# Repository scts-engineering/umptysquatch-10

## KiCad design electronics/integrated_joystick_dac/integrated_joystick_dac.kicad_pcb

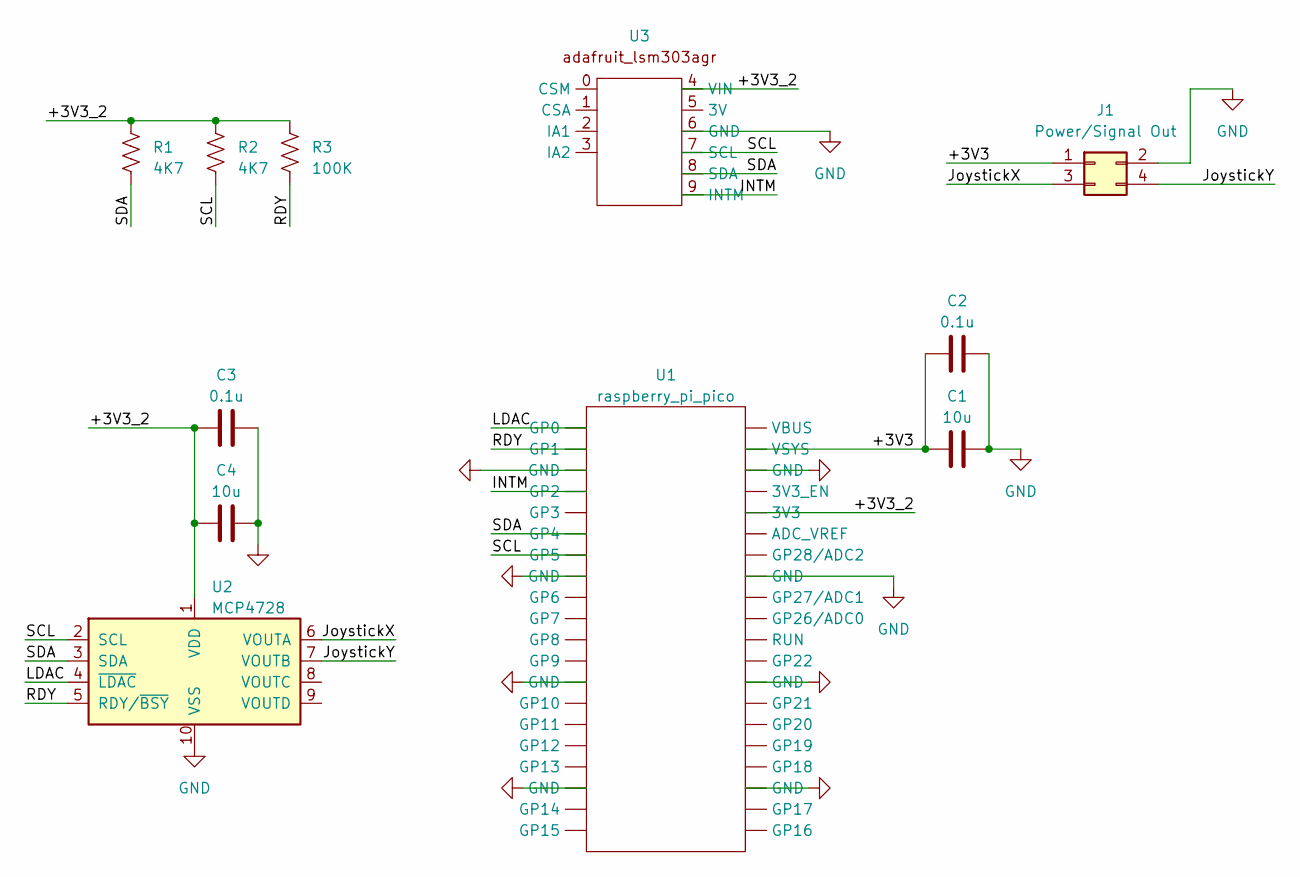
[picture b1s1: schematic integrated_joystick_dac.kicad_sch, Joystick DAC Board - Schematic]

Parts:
C1, C4: 10u; C_0603_1608Metric_Pad1.08x0.95mm_HandSolder
C2, C3: 0.1u; C_0402_1005Metric_Pad0.74x0.62mm_HandSolder
J1: Power/Signal Out; Molex_Mini-Fit_Jr_5569-04A2_2x02_P4.20mm_Horizontal
R1, R2: 4K7; R_Axial_DIN0207_L6.3mm_D2.5mm_P10.16mm_Horizontal
R3: 100K; R_Axial_DIN0207_L6.3mm_D2.5mm_P10.16mm_Horizontal
U1: raspberry_pi_pico
U2: MCP4728; MSOP-10_3x3mm_P0.5mm
U3: adafruit_lsm303agr

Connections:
/+3V3: C1.1, C2.1, J1.1, U1.39 (VSYS)
/+3V3_2: C3.1, C4.1, R1.1, R2.1, R3.1, U1.36 (3V3), U2.1 (VDD), U3.4 (VIN)
/INTM: U1.4 (GP2), U3.9 (INTM)
/JoystickX: J1.3, U2.6 (VOUTA)
/JoystickY: J1.4, U2.7 (VOUTB)
/LDAC: U1.1 (GP0), U2.4 (~LDAC)
/RDY: R3.2, U1.2 (GP1), U2.5 (RDY/~BSY)
/SCL: R2.2, U1.7 (GP5), U2.2 (SCL), U3.7 (SCL)
/SDA: R1.2, U1.6 (GP4), U2.3 (SDA), U3.8 (SDA)
GND: C1.2, C2.2, C3.2, C4.2, J1.2, U1.3 (GND), U1.8 (GND), U1.13 (GND), U1.18 (GND), U1.23 (GND), U1.28 (GND), U1.33 (GND), U1.38 (GND), U2.10 (VSS), U3.6 (GND)

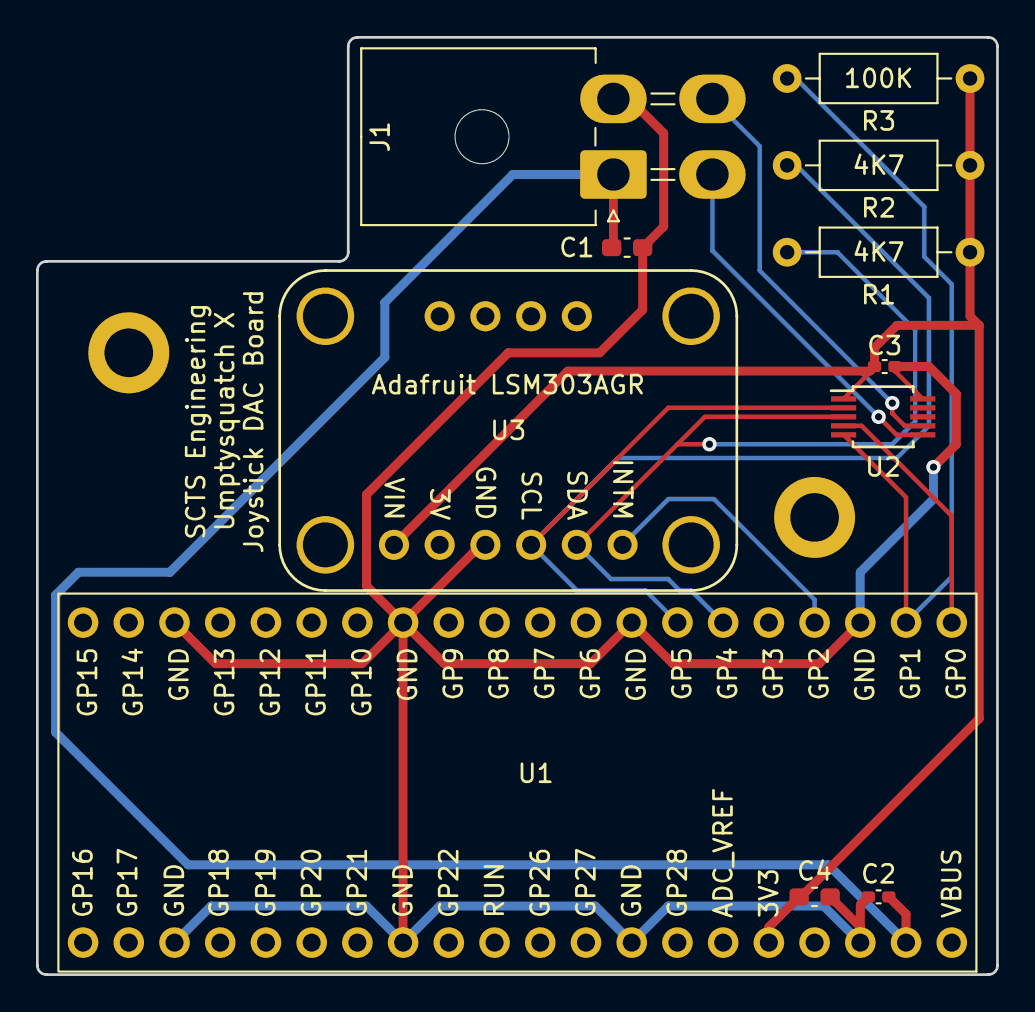
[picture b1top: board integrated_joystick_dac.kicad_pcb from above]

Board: 2 copper layers, 53.3 x 52.1 mm, 11 parts (0 on the bottom side), 10 nets.

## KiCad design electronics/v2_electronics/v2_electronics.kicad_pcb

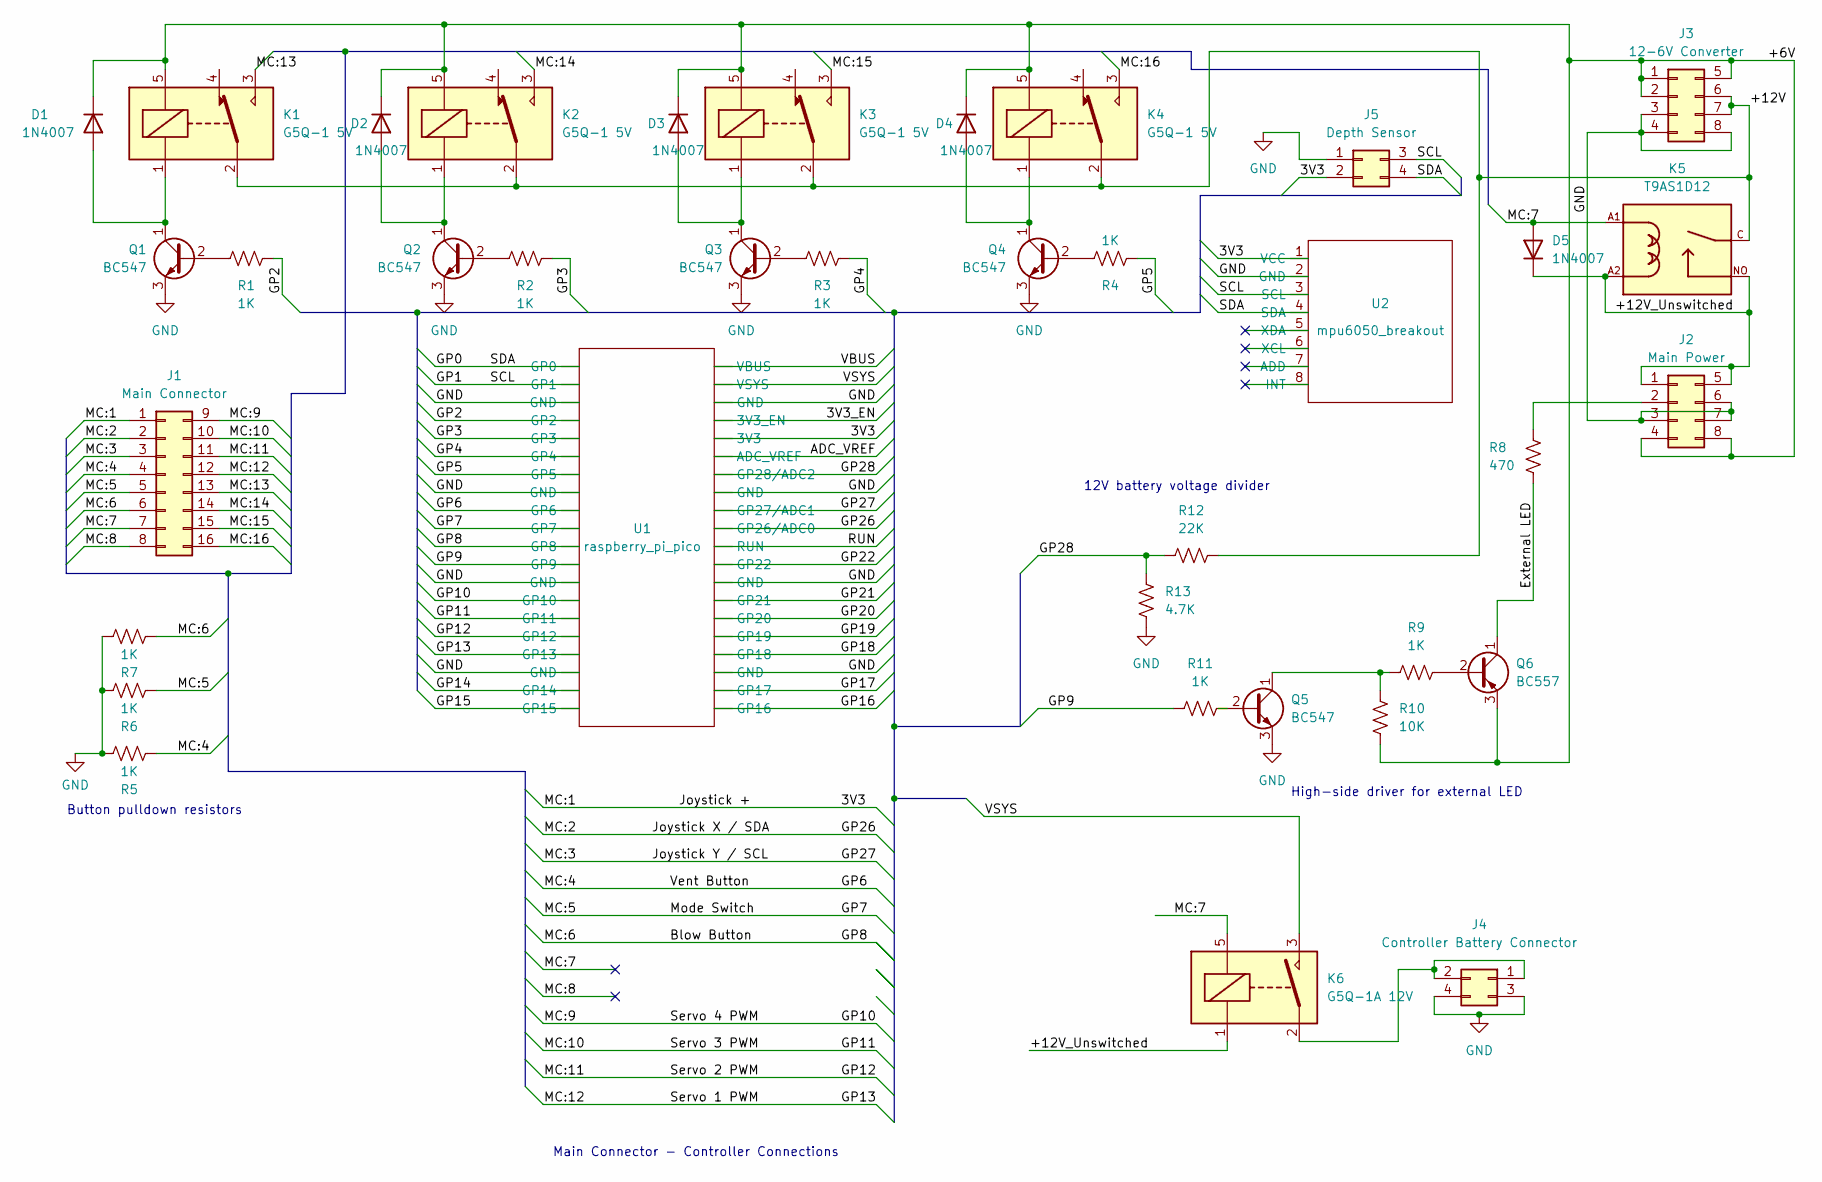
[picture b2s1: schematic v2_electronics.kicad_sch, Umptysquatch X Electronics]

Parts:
D1, D2, D3, D4: 1N4007; D_DO-41_SOD81_P12.70mm_Horizontal
D5: 1N4007; D_DO-41_SOD81_P10.16mm_Horizontal
J1: Main Connector; Molex_Mini-Fit_Jr_5569-16A2_2x08_P4.20mm_Horizontal
J2: Main Power; Molex_Mini-Fit_Jr_5569-08A2_2x04_P4.20mm_Horizontal
J3: 12-6V Converter; Molex_Mini-Fit_Jr_5569-08A2_2x04_P4.20mm_Horizontal
J4: Controller Battery Connector; Molex_Mini-Fit_Jr_5569-04A2_2x02_P4.20mm_Horizontal
J5: Depth Sensor; Molex_Mini-Fit_Jr_5569-04A2_2x02_P4.20mm_Horizontal
K1, K2, K3, K4: G5Q-1 5V; Relay_SPDT_Omron-G5Q-1
K5: T9AS1D12
K6: G5Q-1A 12V; Relay_SPST_Omron-G5Q-1A
Q1, Q2, Q3, Q4, Q5: BC547; TO-92_Inline
Q6: BC557; TO-92_Inline
R1, R2, R3, R4, R5, R6, R7, R9, R11: 1K; R_Axial_DIN0207_L6.3mm_D2.5mm_P10.16mm_Horizontal
R8: 470; R_Axial_DIN0207_L6.3mm_D2.5mm_P10.16mm_Horizontal
R10: 10K; R_Axial_DIN0207_L6.3mm_D2.5mm_P10.16mm_Horizontal
R12: 22K; R_Axial_DIN0207_L6.3mm_D2.5mm_P10.16mm_Horizontal
R13: 4.7K; R_Axial_DIN0207_L6.3mm_D2.5mm_P10.16mm_Horizontal
U1: raspberry_pi_pico
U2: mpu6050_breakout; mpu6050

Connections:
/3V3: J1.1, J5.2, U1.36 (3V3), U2.1 (VCC)
/3V3_EN: U1.37 (3V3_EN); also elsewhere on the board
/+6V: D1.1 (K), D2.1 (K), D3.1 (K), D4.1 (K), J2.4, J2.8, J3.1, J3.2, J3.5, K1.5, K2.5, K3.5, K4.5, Q6.3 (E), R10.1
/+12V: J3.6, J3.7, K1.2, K2.2, K3.2, K4.2, K5.C, R12.2
/+12V_Unswitched: D5.1 (K), J2.1, J2.5, K5.A2, K5.NO, K6.1
/ADC_VREF: U1.35 (ADC_VREF); also elsewhere on the board
/Blow Button: J1.6, R7.2, U1.11 (GP8)
/External LED: Q6.1 (C), R8.1
/GP0: J5.4, U1.1 (GP0), U2.4 (SDA)
/GP1: J5.3, U1.2 (GP1), U2.3 (SCL)
/GP2: R1.2, U1.4 (GP2)
/GP3: R2.2, U1.5 (GP3)
/GP4: R3.2, U1.6 (GP4)
/GP5: R4.2, U1.7 (GP5)
/GP6: J1.4, R5.2, U1.9 (GP6)
/GP7: J1.5, R6.2, U1.10 (GP7)
/GP9: R11.1, U1.12 (GP9)
/GP10: J1.9, U1.14 (GP10)
/GP11: J1.10, U1.15 (GP11)
/GP12: J1.11, U1.16 (GP12)
/GP13: J1.12, U1.17 (GP13)
/GP14: U1.19 (GP14); also elsewhere on the board
/GP15: U1.20 (GP15); also elsewhere on the board
/GP16: U1.21 (GP16); also elsewhere on the board
/GP17: U1.22 (GP17); also elsewhere on the board
/GP18: U1.24 (GP18); also elsewhere on the board
/GP19: U1.25 (GP19); also elsewhere on the board
/GP20: U1.26 (GP20); also elsewhere on the board
/GP21: U1.27 (GP21); also elsewhere on the board
/GP22: U1.29 (GP22); also elsewhere on the board
/GP26: J1.2, U1.31 (GP26/ADC0)
/GP27: J1.3, U1.32 (GP27/ADC1)
/GP28: R12.1, R13.2, U1.34 (GP28/ADC2)
/MC:7: D5.2 (A), J1.7, K5.A1, K6.5
/MC:8: J1.8
/MC:13: J1.13, K1.3
/MC:14: J1.14, K2.3
/MC:15: J1.15, K3.3
/MC:16: J1.16, K4.3
/RUN: U1.30 (RUN); also elsewhere on the board
/VBUS: U1.40 (VBUS); also elsewhere on the board
/VSYS: K6.3, U1.39 (VSYS)
GND: J2.3, J2.6, J2.7, J3.3, J3.4, J3.8, J4.3, J4.4, J5.1, Q1.3 (E), Q2.3 (E), Q3.3 (E), Q4.3 (E), Q5.3 (E), R5.1, R6.1, R7.1, R13.1, U1.3 (GND), U1.8 (GND), U1.13 (GND), U1.18 (GND), U1.23 (GND), U1.28 (GND), U1.33 (GND), U1.38 (GND), U2.2 (GND)
unnamed: D1.2 (A), K1.1, Q1.1 (C)
unnamed: D2.2 (A), K2.1, Q2.1 (C)
unnamed: D3.2 (A), K3.1, Q3.1 (C)
unnamed: D4.2 (A), K4.1, Q4.1 (C)
unnamed: J2.2, R8.2
unnamed: J4.1, J4.2, K6.2
unnamed: Q1.2 (B), R1.1
unnamed: Q2.2 (B), R2.1
unnamed: Q3.2 (B), R3.1
unnamed: Q4.2 (B), R4.1
unnamed: Q5.1 (C), R9.1, R10.2
unnamed: Q5.2 (B), R11.2
unnamed: Q6.2 (B), R9.2

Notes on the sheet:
12V battery voltage divider
Main Connector - Controller Connections
Button pulldown resistors
High-side driver for external LED

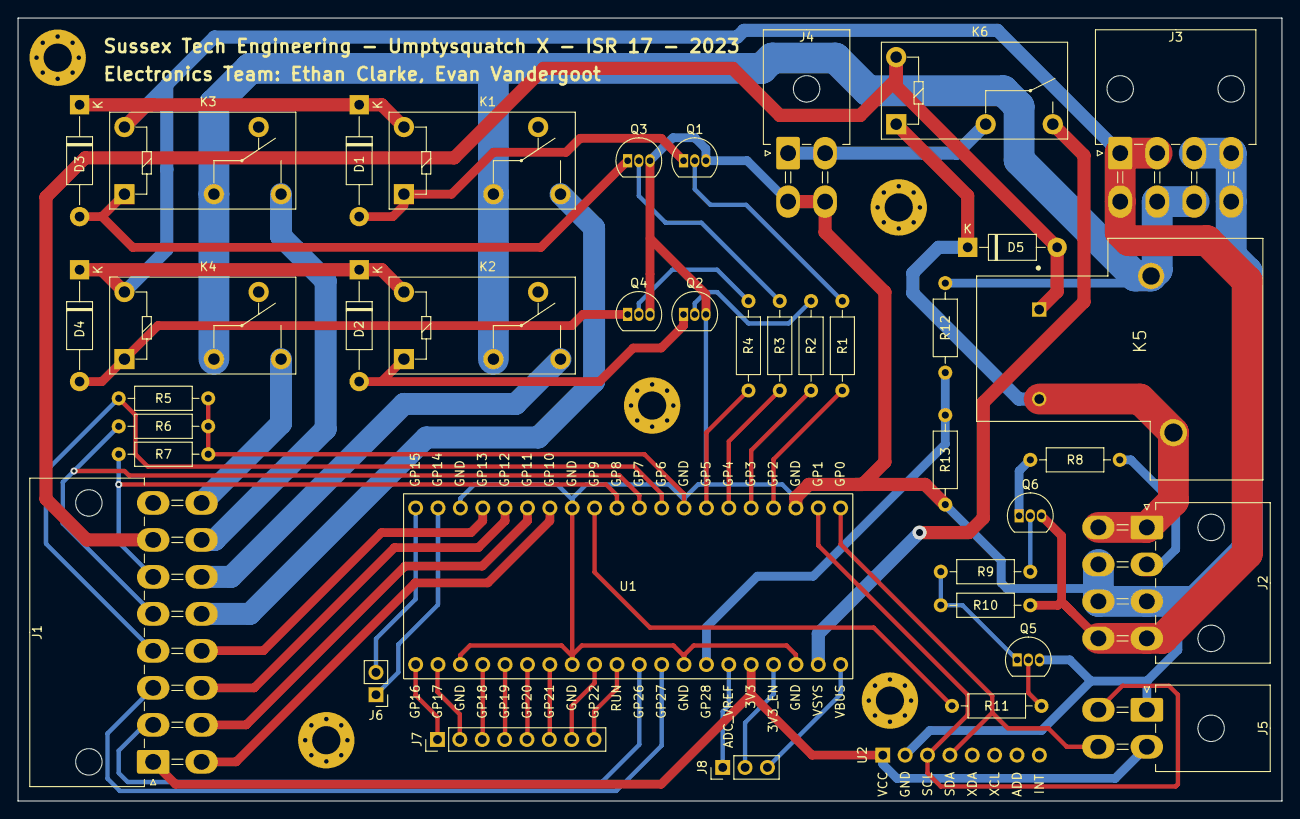
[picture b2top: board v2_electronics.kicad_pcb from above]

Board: 2 copper layers, 143.5 x 88.9 mm, 40 parts (0 on the bottom side), 55 nets.

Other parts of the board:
J6: PinHeader_1x02_P2.54mm_Vertical
J7: PinHeader_1x08_P2.54mm_Vertical
J8: PinHeader_1x03_P2.54mm_Vertical

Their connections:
/3V3_EN: J8.2; also elsewhere on the board
/ADC_VREF: J8.1; also elsewhere on the board
/GP14: J6.1; also elsewhere on the board
/GP15: J6.2; also elsewhere on the board
/GP16: J7.1; also elsewhere on the board
/GP17: J7.2; also elsewhere on the board
/GP18: J7.3; also elsewhere on the board
/GP19: J7.4; also elsewhere on the board
/GP20: J7.5; also elsewhere on the board
/GP21: J7.6; also elsewhere on the board
/GP22: J7.7; also elsewhere on the board
/RUN: J7.8; also elsewhere on the board
/VBUS: J8.3; also elsewhere on the board

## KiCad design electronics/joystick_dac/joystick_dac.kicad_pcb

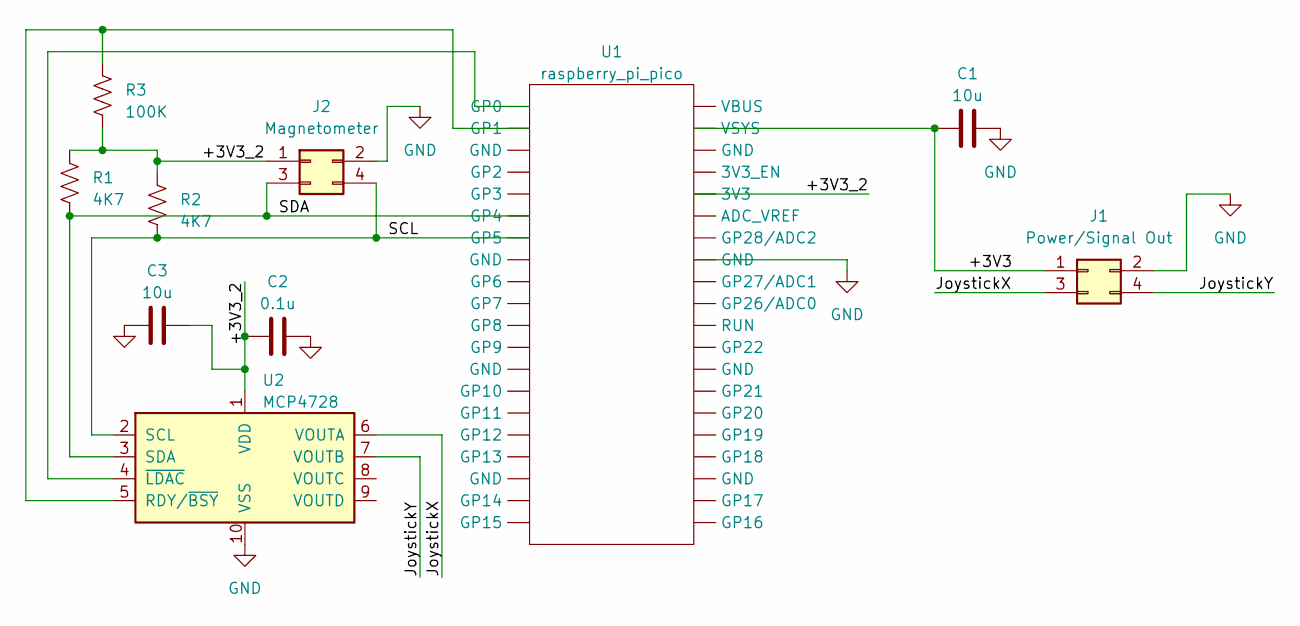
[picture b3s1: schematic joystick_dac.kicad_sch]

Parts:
C1, C3: 10u; C_0603_1608Metric_Pad1.08x0.95mm_HandSolder
C2: 0.1u; C_0402_1005Metric_Pad0.74x0.62mm_HandSolder
J1: Power/Signal Out; Molex_Mini-Fit_Jr_5569-04A2_2x02_P4.20mm_Horizontal
J2: Magnetometer; Molex_Mini-Fit_Jr_5569-04A2_2x02_P4.20mm_Horizontal
R1, R2: 4K7; R_Axial_DIN0207_L6.3mm_D2.5mm_P10.16mm_Horizontal
R3: 100K; R_Axial_DIN0207_L6.3mm_D2.5mm_P10.16mm_Horizontal
U1: raspberry_pi_pico
U2: MCP4728; MSOP-10_3x3mm_P0.5mm

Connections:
/+3V3: C1.1, J1.1, U1.39 (VSYS)
/+3V3_2: C2.1, C3.2, J2.1, R1.1, R2.1, R3.2, U1.36 (3V3), U2.1 (VDD)
/JoystickX: J1.3, U2.6 (VOUTA)
/JoystickY: J1.4, U2.7 (VOUTB)
/SCL: J2.4, R2.2, U1.7 (GP5), U2.2 (SCL)
/SDA: J2.3, R1.2, U1.6 (GP4), U2.3 (SDA)
GND: C1.2, C2.2, C3.1, J1.2, J2.2, U1.33 (GND), U2.10 (VSS)
unnamed: U1.1 (GP0), U2.4 (~LDAC)
unnamed: R3.1, U1.2 (GP1), U2.5 (RDY/~BSY)

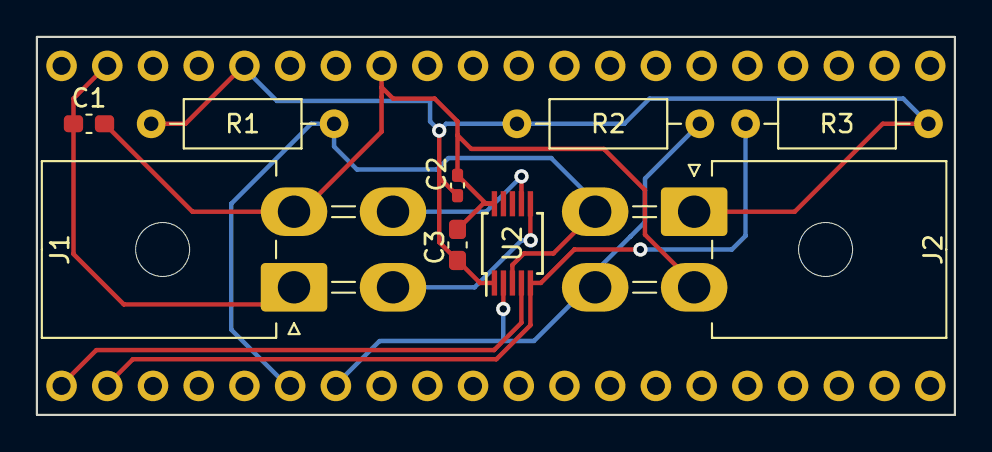
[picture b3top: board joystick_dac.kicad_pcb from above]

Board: 2 copper layers, 51.0 x 21.0 mm, 10 parts (0 on the bottom side), 9 nets.

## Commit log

2022-11-21 outline mostly done
2022-12-02 started re-write of sub program
2022-12-02 add remade old schematic
2022-12-02 added used variables
2022-12-02 make copy for new schematic and pcb
2022-12-05 'complete' old schematic and work on new one
2022-12-05 new code file progress
2022-12-06 for loop done
2022-12-06 more work on new schematic
2022-12-06 finished initial revision of code
2022-12-07 code organization and .gitignore
2022-12-07 work on new pcb
2022-12-09 code organization
2022-12-09 more organization and methods
2022-12-09 some basic wiring for new pcb
2022-12-11 more new pcb work
2022-12-14 'finished' new pcb
2022-12-15 small changes still to new pcb
2022-12-16 arduino wants sub-new.ino in a folder called sub-new
2022-12-22 do some stuff with steering and find out blocking code in mpu6050
2023-01-05 added some depth sensor stuff
2023-01-06 added code for gui joystick map
2023-01-06 joystickrep fixes
2023-01-06 joystickrep stuff 2
2023-01-06 more work joystick magnet stuff
2023-01-10 pin selection and sucessful depth sensor tests
2023-01-11 added testing program
2023-01-11 change test code
2023-01-13 organize folders
2023-01-13 added header file
2023-01-13 joystrickrep thing?
2023-01-13 the servos and x pattern are good now
2023-01-18 added start to led test
2023-01-19 finished led example
2023-01-20 added led to main file
2023-01-30 led stuff
2023-02-03 button testing stuff
2023-02-03 fixed button pin numbers
2023-02-05 added auto and manual mode switching
2023-02-06 spacing fixes
2023-02-06 Work on button switch system
2023-02-06 add magnetometer joystick test to git (for joystickrep)
2023-02-06 random
2023-02-10 added joystick zeroing
2023-02-27 pico combatibility
2023-02-27 remove useless prints to console
2023-03-01 added auto depth bouyancy control
2023-03-01 start v2 electronics schematic
2023-03-01 more work v2 electronics
2023-03-01 added some debug lines
2023-03-03 switch debouncing
2023-03-03 added some changes
2023-03-05 hopefully improve code for debounce
2023-03-06 actually make new debounce work
2023-03-08 more pcb v2 work:
2023-03-09 more work on schematic v2
2023-03-09 more work on v2 schematic:
2023-03-11 start v2 pcb
2023-03-13 do most of the work on v2 pcb
2023-03-14 maybe do some work on the v2 pcb
2023-03-21 'finish' pcbv2, waiting for logo...
2023-03-27 actually have the new debounce work for real this time
2023-03-27 electronics final final?
2023-03-29 add logo to pcb
2023-03-29 new pinmodes
2023-05-02 do lots of stuff
2023-05-06 begin dac thing for joystick
2023-05-07 quick prototype of dac board for joystick
2023-05-08 work on integrated joystick pcb thing
2023-05-08 start redoing board since it's too big
2023-05-09 make smaller board...
2023-05-09 move connector back (probably too far)
2023-05-09 cutout for connector
2023-05-09 fillets are on the wrong layer
2023-05-12 added new pcb code, and cleaned old file
2023-05-17 modify pcb and schematic sheets for export for design report
2023-05-21 some cleanup and folder name changes
2023-06-12 a lot of various improvements and fixes
2023-06-14 add wifi support
